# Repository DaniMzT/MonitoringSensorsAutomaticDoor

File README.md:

# MonitoringSensorsAutomaticDoor
This project is a university thesis carried out in the company GEZE, focused on the automatic sliding doors tested in the laboratory. 
However, it can be extended to generic monitoring projects.
The targets of the project are:
- To acquire data from external sensors (current, temperature, humidity, position, speed and cycles)
- To save the data into a database
- To display live data and maximum/minimum values on a website, as well as providing other functionalities for the test engineers like:
  - Notification of alarms (based on the limits set by the engineers on the website) on the website and by email (email accounts registered on the website)
  - Download some specific data of tests from a specified date range 
  - Watch live streaming of the test benches (FOSCAM IP camera)
  - Perform remote activations on the bench (open/stop)

A NodeMCU is the main controller, acquiring the sensors data and sending the processed data via WiFi to a database (with a PHP file as a bridge).
There is an Arduino UNO for the acquisition of position, speed (both acquired with a home-made encoder: 2 micro photosensors,emitting to and receiving from a zebra band on the door) and limit switch activations (for door cycles).
The communication between NodeMCU and Arduino UNO is via SoftwareSerial --> not very reliable, it is the main issue to be fixed.
Database and website: based on Bitnami WAMP (package for Windows, Apache, MySQL and PHP)

Files in the project:
- Code: website, micros (NodeMCU and Arduino UNO) and database (MySQL)
- KiCAD files (to be added): schematic and printed boards

ISSUES TO BE FIXED:
- Communication between NodeMCU and Arduino UNO. SoftwareSerial is not reliable, I am afraid it is not due to my code. 
I will try to switch ports so that I can use SPI communication (currently, the SPI ports are used as GPIOs)
- Website security is weak. I have been self-learning web programming on the fly --> User identifications, work with JavaScript to process the forms, etc.

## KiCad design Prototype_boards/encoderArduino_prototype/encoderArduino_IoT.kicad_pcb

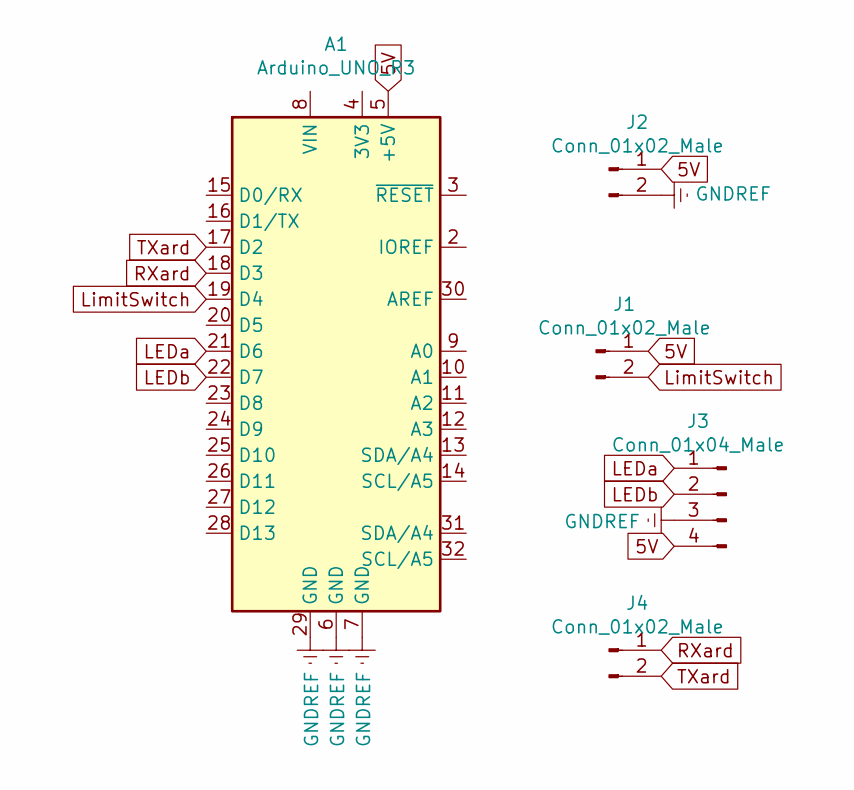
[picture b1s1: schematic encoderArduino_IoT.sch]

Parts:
A1: Arduino_UNO_R3; Arduino_UNO_R3_WithMountingHoles
J1, J2, J4: Conn_01x02_Male; PhoenixContact_MC_1,5_2-G-3.5_1x02_P3.50mm_Horizontal
J3: Conn_01x04_Male; PhoenixContact_MC_1,5_4-G-3.5_1x04_P3.50mm_Horizontal

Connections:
5V: A1.5 (+5V), J1.1, J2.1, J3.4
GNDREF: A1.6 (GND), A1.7 (GND), A1.29 (GND), J2.2, J3.3
LEDa: A1.21 (D6), J3.1
LEDb: A1.22 (D7), J3.2
LimitSwitch: A1.19 (D4), J1.2
RXard: A1.18 (D3), J4.1
TXard: A1.17 (D2), J4.2

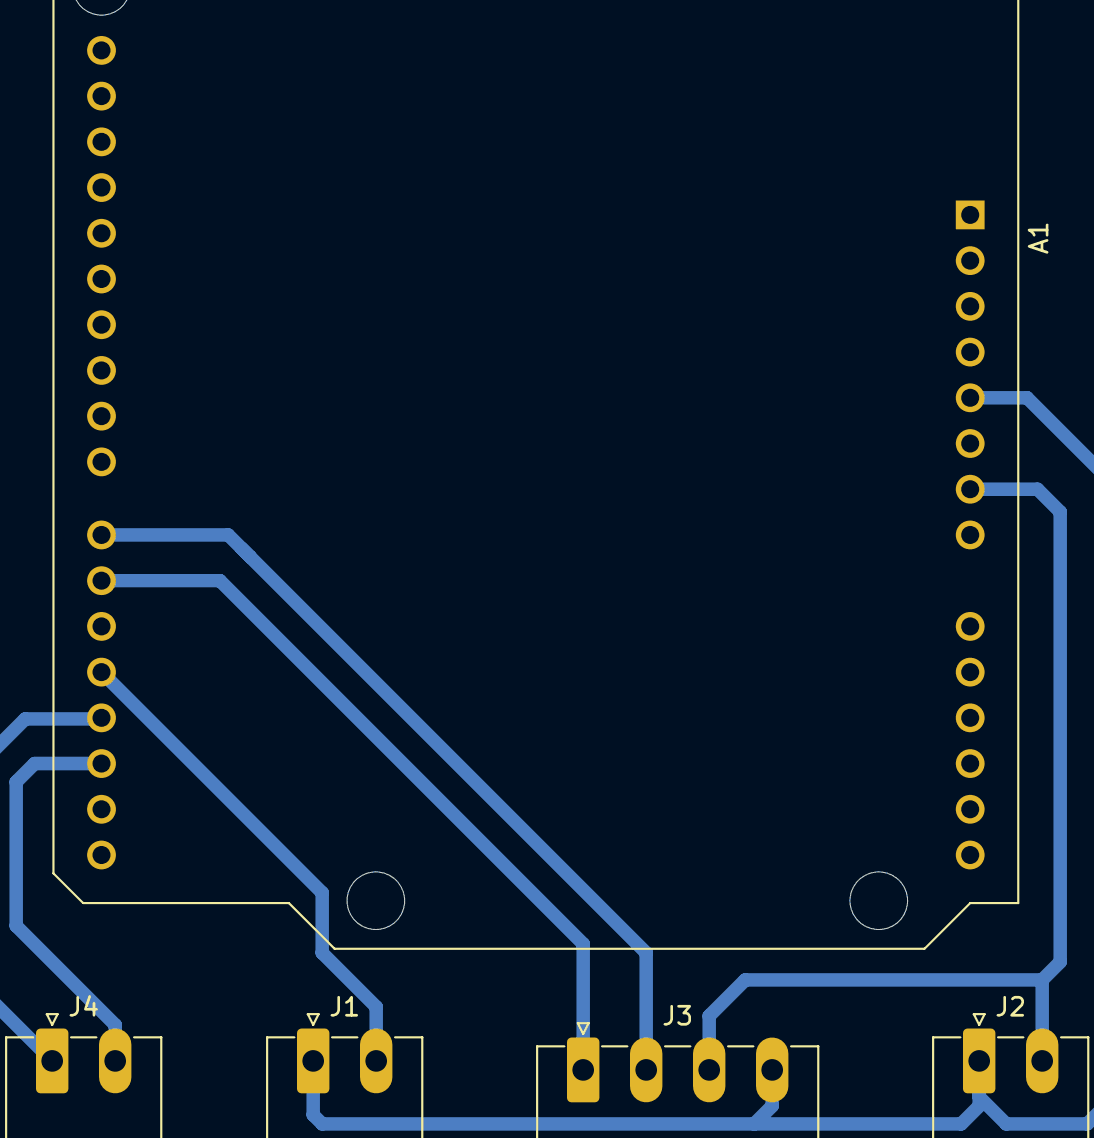
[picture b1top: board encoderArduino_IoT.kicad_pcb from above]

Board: 2 copper layers, 5 parts (0 on the bottom side), 7 nets.

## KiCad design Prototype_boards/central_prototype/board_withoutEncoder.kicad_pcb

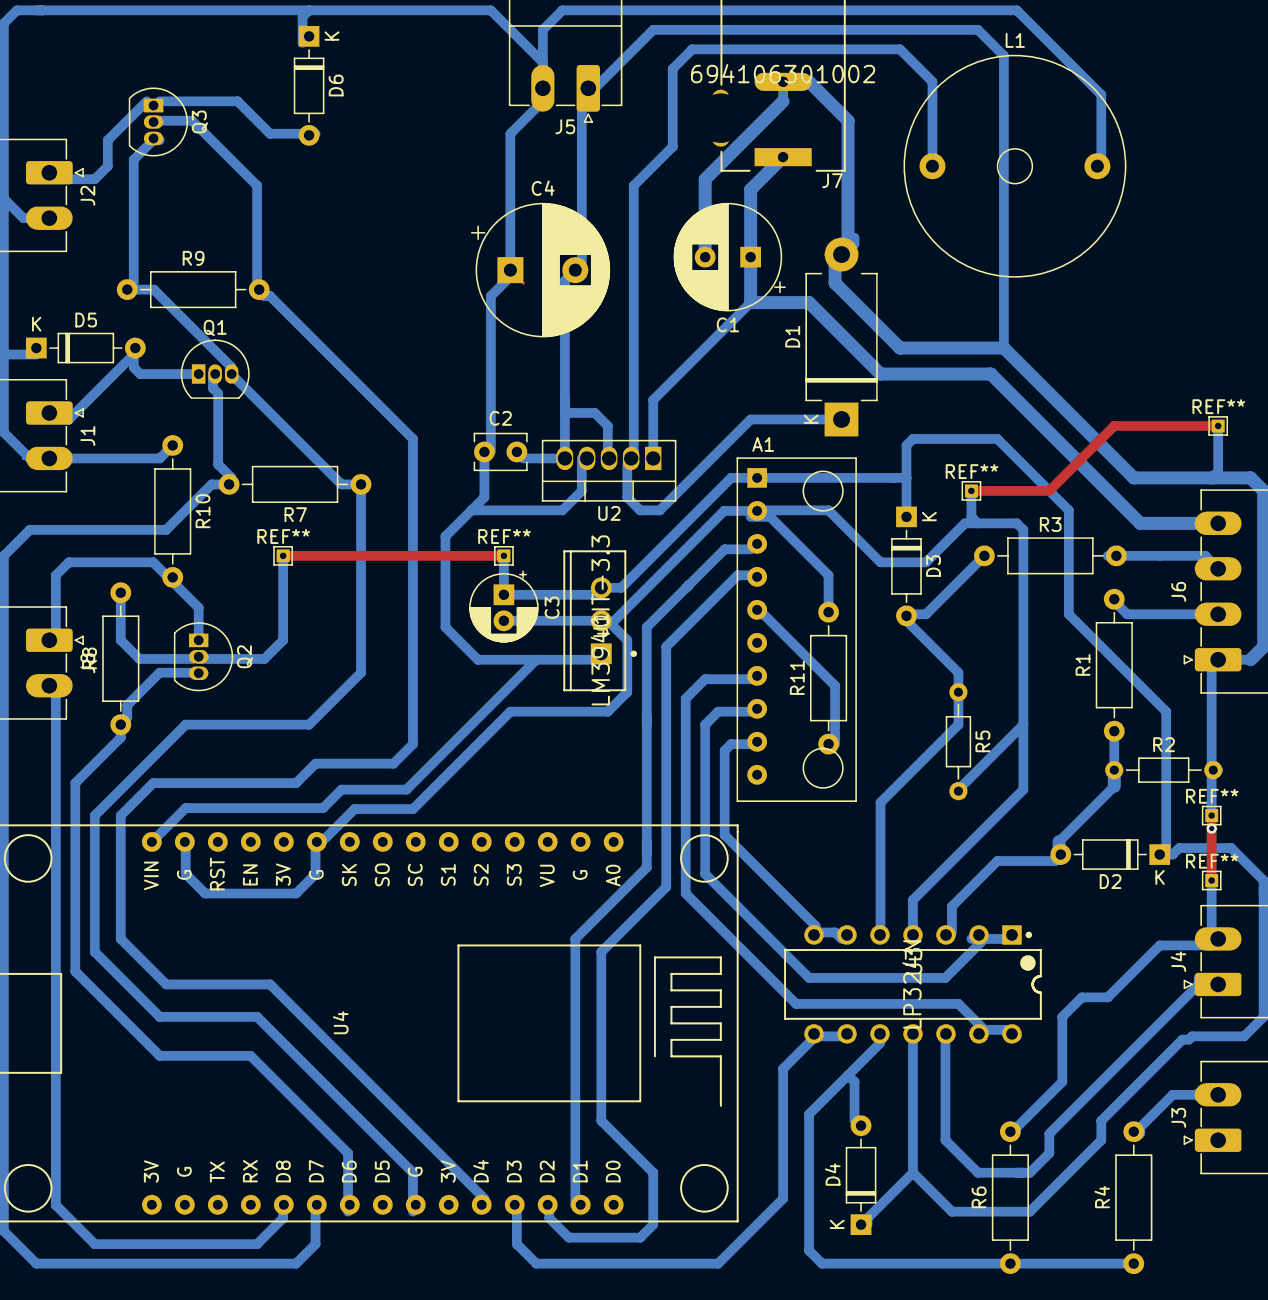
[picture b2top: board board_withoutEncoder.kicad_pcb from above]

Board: 2 copper layers, 38 parts (0 on the bottom side), 26 nets.

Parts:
A1: ADS1115_ADC_Module; ADC1115_ADC_Module
C1: 100uF; CP_Radial_D8.0mm_P3.50mm
C2: 0.47uF; C_Disc_D3.8mm_W2.6mm_P2.50mm
C3: 33uF; CP_Radial_D5.0mm_P2.00mm
C4: 330uF; CP_Radial_D10.0mm_P5.00mm
D1: 1N5822; D_DO-201_P12.70mm_Horizontal
D2, D3, D4, D5, D6: D; D_DO-35_SOD27_P7.62mm_Horizontal
J1, J2, J3, J4, J5, J8: Conn_01x02_Male; PhoenixContact_MC_1,5_2-G-3.5_1x02_P3.50mm_Horizontal
J6: Conn_01x04_Male; PhoenixContact_MC_1,5_4-G-3.5_1x04_P3.50mm_Horizontal
J7: 694106301002; Wurth-694106301002-0-0-0
L1: 330uH; L_Radial_D16.8mm_P12.70mm_Vishay_IHB-1
Q1, Q2, Q3: BS170; TO-92_Inline
R1, R3: 1.8k; R_Axial_DIN0207_L6.3mm_D2.5mm_P10.16mm_Horizontal
R2, R5: 820; R_Axial_DIN0204_L3.6mm_D1.6mm_P7.62mm_Horizontal
R4: 4.7k; R_Axial_DIN0207_L6.3mm_D2.5mm_P10.16mm_Horizontal
R6: 680; R_Axial_DIN0207_L6.3mm_D2.5mm_P10.16mm_Horizontal
R7, R8, R9, R10, R11: 1k; R_Axial_DIN0207_L6.3mm_D2.5mm_P10.16mm_Horizontal
U1: LM3940IT-3.3; TI_National_Semiconductor-LM3940IT-3.3-Manufacturer_Recomme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
U2: LM2575-5.0BT; TO-220-5_Vertical
U3: LP324N; Texas_Instruments-LP324N-Manufacturer_Recommended
U4: NodeMCU_1.0_(ESP-12E); NodeMCU1.0(12-E)

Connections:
3.3V: A1.1, C3.1, D2.1, D3.1, D4.1, Q2.2, R8.2, U1.3, U3.11
5V: C2.1, C4.1, D5.1, D6.1, J1.2, J2.2, J5.2, L1.2, R10.1, U1.1, U2.4, U4.15
24V: C1.1, J6.4, J7.1, U2.1
Current_Fluke: J4.1, U3.12
GNDREF: A1.2, C1.2, C2.2, C3.2, C4.2, D1.2, J4.2, J5.1, J6.1, J7.2, Q1.3, Q3.3, R2.2, R5.2, R6.2, R7.1, R9.1, R11.2, U1.2, U2.3, U2.5, U3.4, U4.10, U4.14, U4.17, U4.24
Humidity_sensor: J6.2, R1.2
KB_out: Q1.2, R7.2, U4.21
KB_relay: D5.2, J1.1, Q1.1
unnamed: A1.5, R11.1
unnamed: D1.1, L1.1, U2.2
unnamed: D2.2, R1.1, R2.1, U3.3
unnamed: D3.2, R3.1, R5.1, U3.5
unnamed: D4.2, R4.1, R6.1, U3.10
RXard: J8.2, U4.20
RXnode: Q2.3, R8.1, U4.22
SCL: A1.3, U4.29
SDA: A1.4, U4.28
Stop_from_DCU: J3.2, R4.2
TXard: J8.1, Q2.1, R10.2
Temperature_sensor: J6.3, R3.2
current: A1.7, U3.13, U3.14
humidity: A1.8, U3.1, U3.2
stop_in: U3.8, U3.9, U4.27
stop_out: Q3.2, R9.2, U4.26
stop_relay: D6.2, J2.1, Q3.1
temperature: A1.9, U3.6, U3.7

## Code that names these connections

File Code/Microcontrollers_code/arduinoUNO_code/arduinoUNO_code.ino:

#include <SoftwareSerial.h> //for software serial communication Arduino-NodeMCU
#include <StreamUtils.h>

const int pinCOUNTER = 4 ; //pin D4 GPIO4 limit switch used as a cycles counter
const int pinLEDA = 6; //pin D6 GPIO6 for LED A used for the encoder
const int pinLEDB = 7; //pin D7 GPIO7 for LED B used for the encoder

bool addCycle = true; //true if new cycle. the number of cycles is stored in database. bool size=1 byte; int size = 2 bytes (if I wanted to use 1 or 0 instead of true or false)
int lastCounter = LOW; //last state of the limit switch. HIGH/LOW from digitalRead is type int
int currentCounter = LOW; //current state of the limit switch
unsigned long time_cycle_begin = millis(); //time when cycle starts. millis() is type unsigned long
unsigned long time_cycle_previous = millis(); //time reading in the previous iteration
unsigned long time_cycle_current = millis(); //current time
float duration_cycle; //duration of the current cycle in seconds.
bool encoder_lost = false; //if encoder reading makes no sense (encoder error, either due to the sensor or to wrong reading because of too slow sampling, etc)
int LEDA; //signal LED A
int LEDB; //signal LED B
unsigned int last_Encoder_state = 4; //last encoder reading.state = 0 if{HIGH,LOW};1 if{LOW,HIGH};2 if{LOW,LOW};3 if{HIGH,HIGH};4=to access case:default first time in readEncoder
const int resolution_position = 3; //displacement in mm in every transition
int previous_position = -1; //positioning/speed will start when position==0. BETTER UNSIGNED! if the installation is correct, signed will work
int current_position = -1; //positioning/speed will start when position==0. BETTER UNSIGNED! if the installation is correct, signed will work
float current_speed = -1.0;
bool initialized = false;

//pins SW serial
const int RXard = 2; //GPIO2
const int TXard = 3; //GPIO3
SoftwareSerial swSerial(2,3); //communication SW serial Arduino-NodeMCU

//int iteration = 0;
bool ack_Node = false;
const byte limit_wait = 10; //limit to wait for the permission from Node. As short as possible to keep encoder running
unsigned int time_ArdNode = 0;

const int loop_wait = 1; //ms of wait between loop iterations
char rubbish;

void setup() {
  Serial.begin(115200); //serial port (real port)
  // Using the lowest possible data rate to reduce error ratio
  swSerial.begin(4800);//4800. 9600 was proved to work
  pinMode(pinLEDA,INPUT); //configuration digital input
  pinMode(pinLEDB,INPUT); //configuration digital input
  pinMode(pinCOUNTER,INPUT); //configuration digital input
  delay(5000);
  while (swSerial.available()!=0) {
    //setup.swSerial != 0
    rubbish = swSerial.read();
  }
  //setup.swSerial empty
  swSerial.print('N');
  
}

void loop() {
  readCounter(pinCOUNTER); //check if there is a new cycle by reading limit switch
  readEncoder(pinLEDA, pinLEDB); //position and speed calculated after reading from encoder
  ack_Node = false;
  time_ArdNode = millis();
  //send as long as Node allows ('y' received)
  while ((swSerial.available()>0)&&(ack_Node == false)&&((millis()-time_ArdNode)<limit_wait)){
    if (swSerial.read()=='S'){
      ack_Node = true;
    }
  }
  if (ack_Node == true) {
    swSerial.print('Y');//yes
    swSerial.print('<'); //start marker: <
    swSerial.print(current_position);
    swSerial.print(';');
    swSerial.print(current_speed);
    swSerial.print(';');
    swSerial.print(duration_cycle);
    swSerial.print(';');
    swSerial.print(addCycle);
    swSerial.print(';');
    swSerial.print(encoder_lost);
    swSerial.print('>');//end marker: >
  }
  
  delay(loop_wait);
}

void readCounter(int pin) {
  currentCounter = digitalRead(pin);
  addCycle = false;
  if ((currentCounter == HIGH) && (lastCounter == LOW)) { //rising edge
    initialized = true;
    //current_position = 0;
    /*Not desired to do current_position=0. If limit switch active, current pos GIVEN BY ENCODER CALCULATION should be 0.otherwise, encoder may be faulty, but we want to know encoder
      is faulty by comparing curr pos and limit switch.As well,maybe position is close to 0 but not 0 when limit switch active.If we wanted to do current_position=0,anyway we should
      modify readEncoder because currently current_position=previous_position(w/o +-resolution)*/
    addCycle = true;
    time_cycle_begin = millis();
    duration_cycle = 0;
  }
  lastCounter = currentCounter;
}

void readEncoder(int pinA, int pinB) {
  if (initialized == true) { //initialized once we know the zero position.From then, we can know absolute position.
    //switch-case only can work with integers or enumerations.
    //if statements working element by element, not array_variable == {value1,value2...} but array_variable[0]==value1 && array_variable[1]==value2 ...
    //only read encoder if last reading was not defective or,if defective,restart after every new cycle
    if ((encoder_lost == false) || ((encoder_lost == true) && (addCycle == true))) {
      encoder_lost = false; //clear encoder error
      LEDA = digitalRead(pinA);
      LEDB = digitalRead(pinB);
      time_cycle_current = millis();
      //machine of encoder states according to LED A and LED B signals
      if ((LEDA == HIGH) && (LEDB == LOW)) { //state 0
        switch (last_Encoder_state) {
          case 0:
            current_position = previous_position;
            break;
          case 2:
            current_position = previous_position + resolution_position;
            break;
          case 3:
            current_position = previous_position - resolution_position;
            break;
          case 1: //encoder lost
            encoder_lost = true;
          default:
            current_position = previous_position;
            break;
        }
        last_Encoder_state = 0;
      }
      else if ((LEDA == LOW) && (LEDB == HIGH)) { //state 1
        switch (last_Encoder_state) {
          case 1:
            current_position = previous_position;
            break;
          case 3:
            current_position = previous_position + resolution_position;
            break;
          case 2:
            current_position = previous_position - resolution_position;
            break;
          case 0: //encoder lost
            encoder_lost = true;
          default:
            current_position = previous_position;
            break;
        }
        last_Encoder_state = 1;
      }
      else if ((LEDA == LOW) && (LEDB == LOW)) { //state 2
        switch (last_Encoder_state) {
          case 2:
            current_position = previous_position;
            break;
          case 1:
            current_position = previous_position + resolution_position;
            break;
          case 0:
            current_position = previous_position - resolution_position;
            break;
          case 3: //encoder lost
            encoder_lost = true;
          default:
            current_position = previous_position;
            break;
        }
        last_Encoder_state = 2;
      }
      else if ((LEDA == HIGH) && (LEDB == HIGH)) { //state 3
        switch (last_Encoder_state) {
          case 3:
            current_position = previous_position;
            break;
          case 0:
            current_position = previous_position + resolution_position;
            break;
          case 1:
            current_position = previous_position - resolution_position;
            break;
          case 2: //encoder lost
            encoder_lost = true;
          default:
            current_position = previous_position;
            break;
        }
        last_Encoder_state = 3;
      }
      duration_cycle = (time_cycle_current - time_cycle_begin ) / 1000.0; // converted into seconds, as millis() are given in ms
      current_speed = (float(current_position) - float(previous_position)) * 1000.0 / (float(time_cycle_current - time_cycle_previous)); //substraction unsigned int returns an unsigned int
      time_cycle_previous = time_cycle_current;
      previous_position = current_position;
    }
  }
  else {
    time_cycle_previous = millis(); //for the first time in readEncoder
  }
}

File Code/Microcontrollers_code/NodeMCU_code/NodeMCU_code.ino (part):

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ESP8266WebServer ESPserver(5000); //default:80.use 5000 to avoid issues,as defined in port forwarding.But when clicking the button, a warning window will appear

//SENSORS. PINMODE --> GPIO number, no D1,D2...
const int pinCURRENT = 0; //pin of ADS1115 for sensor of current. Notation used in readADC_SingleEnded()
const int pinTEMP = 2; //pin of ADS1115 for temperature sensor. Notation used in readADC_SingleEnded()
const int pinHUM = 1; //pin of ADS1115 for humidity sensor. Notation used in readADC_SingleEnded()
const int pinSTOP_out = 2; //pin D4 GPIO2 for STOP relay managed from web
const int pinKB = 13; //pin D7 GPIO13 for KB, managed from web
const int pinSTOP = 3; //pin of ADS1115 for emergency stop button activated in the test site

const float adc_res = 0.125;
const float sensitivity_Current = adc_res*300/33;//Fluke i30 sensitivity current/ADC resolution = (30000mA/3000mV)*(3000mV/3300mV)*0.125mV/bitADC
const int offset_Current = 0;//offset current given in mA
const int offset_OAc = 0; //offset current due to operational amplifier, given in bits
float current = 0; //mA
const float sensitivity_Temp = adc_res*5/313; //sensitivity temp/ADC resolution = ((50-(0))/10000mV)*(10000mV/3130mV)*0.125mV/bitADC
const int offset_Temp = 0; //offset temperature due to sensor
const int offset_OAt = 0; //-3600.offset temperature due to operational amplifier, given in bits
float temperature = 0;
const float sensitivity_Hum = adc_res*9/313; //sensitivity hum/ADC resolution = (90/10000mV)*(10000mV/3300mV)*0.125mV/bitADC
const int offset_Hum = 5; //offset humidity due to sensor
const int offset_OAh = 0; //-3456 offset humidity due to operational amplifier, given in bits
unsigned int humidity = 0;
int EmergencyStop_active = LOW; //signal from Emergency Stop button
//raw values ADC
int16_t rawT = 0; 
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
    //ESP8266 AS CLIENT,STARTING CONNECTION TO SEND DATA
    readPositionSpeed();//read position, speed, cycle duration, new cycle, encoder lost (error)
    readAnalogue(pinCURRENT, pinTEMP, pinHUM, pinSTOP); //reading current sensors and input stop

    //data to be sent. DO NOT USE '?'in front,it seems http.POST already takes it into account
    String data = "T=" + String(temperature) + "&H=" + String(humidity) + "&C=" + String(current) + "&P=" + String(current_position) + "&S=" + String(current_speed);
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
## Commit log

2022-02-18 First commit with the code for micros, web and database
2022-05-23 adding prototypes
